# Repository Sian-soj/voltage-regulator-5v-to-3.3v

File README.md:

# 5V to 3.3V Linear Voltage Regulator PCB

A compact, custom-designed printed circuit board (PCB) developed in KiCad to regulate a 5V input down to a stable 3.3V output. This board is engineered specifically to provide clean power to microcontrollers, sensors, and low-voltage embedded systems.

## 🚀 Overview

The core of this design utilizes the *AMS1117-3.3* low-dropout (LDO) linear regulator. The project served as an immersive hands-on exercise in hardware design, focusing on tight form-factor optimization, power distribution routing, and custom footprint creation.

### Key Specifications
* *Regulator IC:* AMS1117-3.3 (SOT-223 package)
* *Input Voltage:* 5V DC
* *Output Voltage:* 3.3V DC
* *Form Factor:* Optimized for minimal PCB surface area

---

## 📸 Design Preview

| 3D Render (Top View) | Schematic Preview |
|---|---|
|  |  |

---

## 🛠️ Design & Engineering Challenges Overcome

* *Form Factor Optimization:* Focused heavily on keeping the layout as compact as possible, minimizing trace lengths while ensuring stable performance.
* *Power Distribution Network (PDN):* Structured a directional layout—isolating the 5V input path on one side and routing the 3.3V output rails on the opposite side to minimize cross-talk and maximize power efficiency.
* *Custom Footprints:* Designed custom component footprints to move away from generic libraries, allowing tailored component spacing and layout flexibility.
* *Trace Navigation:* Solved routing puzzles in highly constrained spaces while maintaining proper clearance for power traces and grounding.

---

## 📁 Repository Structure

├── Hardware/          # KiCad project files (.kicad_prl, .kicad_sch, .kicad_pcb)  
├── Production/        # Gerber files (zip) and Bill of Materials (BOM) for fabrication  
├── images/            # 3D renders, schematic and footprint screenshots for documentation  
└── README.md          # Project documentation  

## 📈 Future Steps
* Order physical prototypes for manufacturing.
* Component sourcing and manual SMD soldering.
* Multimeter and oscilloscope testing to verify voltage stability and ripple management under load.

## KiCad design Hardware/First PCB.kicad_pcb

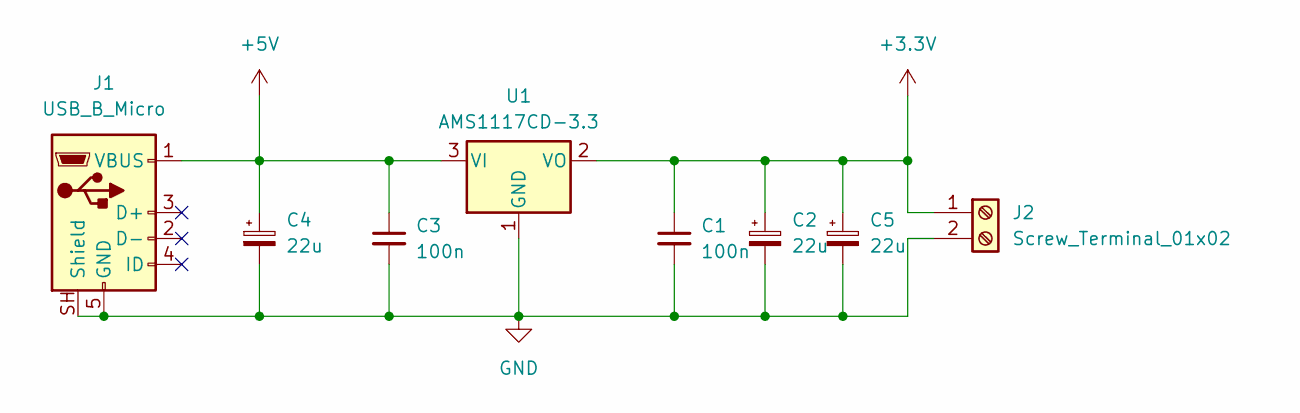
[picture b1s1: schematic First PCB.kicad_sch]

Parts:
C1, C3: 100n; C_0402_1005Metric
C2, C4, C5: 22u; C_Elec_6.3x7.7
J1: USB_B_Micro; USB_Micro-B_Molex_47346-0001
J2: Screw_Terminal_01x02; TerminalBlock_Phoenix_MKDS-3-2-5.08_1x02_P5.08mm_Horizontal
U1: AMS1117CD-3.3; TO-252-3_TabPin2

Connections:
+3.3V: C1.1, C2.1, C5.1, J2.1, U1.2 (VO)
+5V: C3.1, C4.1, J1.1 (VBUS), U1.3 (VI)
GND: C1.2, C2.2, C3.2, C4.2, C5.2, J1.5 (GND), J1.SH (Shield), J2.2, U1.1 (GND)

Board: 2 copper layers, 8 parts (0 on the bottom side), 3 nets, no tracks yet.

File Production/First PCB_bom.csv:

"Id";"Designator";"Footprint";"Quantity";"Designation";"Supplier and ref";
1;"C1, C3";"C_0402_1005Metric";2;"100n";;;
2;"C2, C4, C5";"C_Elec_6.3x7.7";3;"22u";;;
3;"J1";"USB_Micro-B_Molex_47346-0001";1;"USB_B_Micro";;;
4;"J2";"TerminalBlock_Phoenix_MKDS-3-2-5.08_1x02_P5.08mm_Horizontal";1;"Screw_Terminal_01x02";;;
5;"U1";"TO-252-3_TabPin2";1;"AMS1117CD-3.3";;;

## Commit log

2026-06-24 Add content to not.txt
2026-06-24 Create
2026-06-24 Create aa
2026-06-24 Rename 3d view.png to 3d_view.png
2026-06-24 Revise README for 5V to 3.3V Voltage Regulator PCB
    Expanded project documentation with detailed specifications, design challenges, and repository structure.
